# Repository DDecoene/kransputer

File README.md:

# kransputer

## What Kransputer is

Kransputer is a working computer built from a few thousand discrete CMOS
transistors — a machine on the scale of an Intel 4004, but made of parts you can
hold — designed to grow into a multiprocessor: one core, then a ring of up to
eight, passing messages the way INMOS's Transputer did. It exists to be
understood and rebuilt, by a person, a class or a hackerspace. Not to be sold.

## Why it looks the way it does

One decision forces everything else: CMOS. Almost every discrete-transistor
computer ever built is NMOS and burns about a watt standing still. CMOS costs
twice the transistors but makes power scale with clock rate instead — turn the
clock down and the machine sips. Staying inside a small transistor budget is why
the design is stripped to the bone:

- **One instruction** — subleq only, so there is no decoder. The instruction set
  lives in the assembler as macros.
- **A few bits at a time** — a serial datapath, so the arithmetic unit is a
  handful of adders. You pay in clock cycles, which are cheap.
- **No bus** — memory, display and input all speak SPI over four wires. No
  address bus, no data bus.

On this machine, talking to the core next door is cheaper than reading your own
memory. That is why the ring is the point, not an afterthought.

## How it gets built — from the ground up

The architecture is settled on paper: a SUBLEQ core with a serial datapath and
SPI links, meant to grow into a message-passing ring. What is deliberate is the
direction of the work. Instead of proving the whole machine on an FPGA before
touching a soldering iron, Kransputer is built upward from real gates, one
module at a time.

1. **Gates** — small PCBs, each a fistful of MOSFETs forming one logic function
   (NAND, NOR, NOT …), that plug into a breadboard and share a common bus. This
   is the layer built so far.
2. **Blocks** — those gates wired into the units the design calls for: the serial
   adder that is the whole ALU, the registers, the subleq sequencer and bit
   counter, the SPI interface to memory, the four-wire link to the next core.
   Each block is first modelled in structural Verilog — gate for gate, built
   from the same NAND/NOR/NOT cells as the boards — and checked in simulation,
   then built physically on breadboards.
3. **A core** — one complete processor, assembled from the blocks.
4. **A ring** — the core replicated and connected: two, then four, then eight,
   blocking on the links for synchronisation.

The structural model is the reference: the same stimulus into the simulation and
into the breadboard must give the same result, or the block is wrong.

## Status

The gate boards are drawn but **not yet routed** — schematics and rough
placement are done, copper is not. Work right now is on the first blocks in
structural Verilog, which land here soon. Once those hold up in simulation the
boards get routed and finished for a first self-ordered run, with build notes
and other material alongside.

## This repository

Discrete-logic building blocks for the kransputer — the **Gates** layer above.
Each module is a small PCB that plugs into a breadboard on two opposite edge
headers carrying an identical 16-pin pass-through bus, so modules can sit side by
side across one or more breadboards and be wired together into larger logic.

## Boards

| TARGET      | Board                                    |
|-------------|-------------------------------------------|
| `nand`      | 4x discrete static-CMOS 2-input NAND      |
| `nor`       | 4x discrete static-CMOS 2-input NOR       |
| `not`       | 6x discrete static-CMOS inverter          |
| `indicator` | 12-channel buffered bus LED indicator     |

Logic FETs are AO3400A (N-channel) / AO3401A (P-channel) in SOT-23.

The logic boards carry **no** indicator parts. Every node is on the bus; the
indicator board buffers each signal with a single AO3400A in common source (its
gate is high-impedance, so the logic net is not loaded) that sinks an LED fed
from the indicator board's own VDD rail. **LED lit = logic 1.** Watching the
machine therefore does not sag the logic levels.

## Bus pinout

Both edge headers (`J1`, `J2`) carry the same 16 pins, wired 1:1, so any signal
is reachable from either edge. Framing is fixed: pin 1 = VDD, pin 2 = GND,
pins 3–14 carry the 12 signal nets the board drives, pins 15/16 are the
edge-to-edge spares (`BUS_X`, `BUS_Y`).

`J1`/`J2` are stacking headers: male tails point down into the breadboard,
female sockets face up so the indicator shield can plug onto the same 16 pins.

### Signal nets per board (bus pins 3–14)

| Pin | `nand`   | `nor`   | `not`      | `indicator` |
|-----|----------|---------|------------|-------------|
| 3   | NAND_1_A | NOR_1_A | NOT_1_IN   | SIG1        |
| 4   | NAND_1_B | NOR_1_B | NOT_1_OUT  | SIG2        |
| 5   | NAND_1_Y | NOR_1_Y | NOT_2_IN   | SIG3        |
| 6   | NAND_2_A | NOR_2_A | NOT_2_OUT  | SIG4        |
| 7   | NAND_2_B | NOR_2_B | NOT_3_IN   | SIG5        |
| 8   | NAND_2_Y | NOR_2_Y | NOT_3_OUT  | SIG6        |
| 9   | NAND_3_A | NOR_3_A | NOT_4_IN   | SIG7        |
| 10  | NAND_3_B | NOR_3_B | NOT_4_OUT  | SIG8        |
| 11  | NAND_3_Y | NOR_3_Y | NOT_5_IN   | SIG9        |
| 12  | NAND_4_A | NOR_4_A | NOT_5_OUT  | SIG10       |
| 13  | NAND_4_B | NOR_4_B | NOT_6_IN   | SIG11       |
| 14  | NAND_4_Y | NOR_4_Y | NOT_6_OUT  | SIG12       |

The bus is positional: `J1` pin k ≡ `J2` pin k on every board. The indicator
shield taps pins 3–14 as `SIG1..SIG12` and shows whatever a neighbouring board
drives there.

Supply: 5 V on the bus. The two header rows are 0.9" apart (row `a` to row `j`
of one breadboard); columns b–e and f–i stay free for patch wires.

## Build

```bash
python3 -m venv venv
./venv/bin/pip install -r requirements.txt

./venv/bin/python circuit.py             # writes every <target>_module.net
./venv/bin/python circuit.py nand        # or just one
```

`kicad_env.py` finds the KiCad symbol libraries at the macOS bundle path
(`/Applications/KiCad/KiCad.app/...`). On Linux or Windows, set the
`KICAD*_SYMBOL_DIR` / `KICAD*_FOOTPRINT_DIR` environment variables to your
install's library paths before running, or adjust `kicad_env.py`.

1. Turn the netlist into a board. Either open a new PCB project `nand_module/`
   in KiCad and "Update PCB from Netlist", or run `kinet2pcb` headless (needs
   `skidl`, `kinparse` and `pcbnew` on the *same* Python — i.e. installed into
   KiCad's bundled Python, since `pcbnew` is not in the venv):
   ```bash
   kinet2pcb -i nand_module.net -o nand_module/nand_module.kicad_pcb -w --overwrite
   ```
2. Rough auto-placement — run from the folder that contains `nand_module/`,
   using KiCad's bundled Python:
   ```bash
   /Applications/KiCad/KiCad.app/Contents/Frameworks/Python.framework/Versions/3.9/bin/python3 \
       place.py nand
   ```
   `place.py` positions J1/J2 on opposite 0.9" edges, clusters each gate between
   them, draws a tight `Edge.Cuts` rectangle and pours a `B.Cu` GND zone. Pass an
   explicit `.kicad_pcb` path as a second argument to place a board elsewhere.
3. Reopen in KiCad, nudge, route. Re-fill the GND zone. Run DRC.
4. Plot Gerbers.

Repeat with `nor`, `not`, and `indicator` (each is its own KiCad project in its
own `<target>_module/` folder). `nand_module/`, `nor_module/`, `not_module/` and
`indicator_module/` are checked in.

### Fan-out

A discrete gate output driving other **gate** inputs is limited by speed, not
current (CMOS inputs are capacitive) — fine at this machine's speeds. One
indicator-board channel adds roughly the AO3400A gate capacitance to the net it
watches; one indicator board on the bus is negligible.

## Tests

```bash
./venv/bin/pytest
```

The placement integration test is skipped unless `kinet2pcb` can import
`pcbnew` (it cannot from the venv). `place.py` uses fixed, hand-computed
coordinates per board type, so its output is deterministic and easy to
eyeball in KiCad.

## Layout

- `circuit.py`  — SKiDL netlist generator (all boards, no arg = build every one)
- `place.py`    — pcbnew layout: exact positions per board type, Edge.Cuts, GND pour
- `kicad_env.py`— points SKiDL at the bundled KiCad libraries on macOS
- `SYMBOLS.md`  — resolved KiCad symbols (AO3400A/AO3401A, LED, R array, header)
- `tests/`      — SKiDL-netlist topology checks per board + CLI + place integration

## Licence

[PolyForm Noncommercial License 1.0.0](LICENSE). Build it, study it, modify it,
teach with it, and contribute — freely, for any noncommercial purpose. Selling
kits, boards, or hardware based on this work is reserved to the maintainer; see
[COMMERCIAL.md](COMMERCIAL.md). Contribution terms are in
[CONTRIBUTING.md](CONTRIBUTING.md).

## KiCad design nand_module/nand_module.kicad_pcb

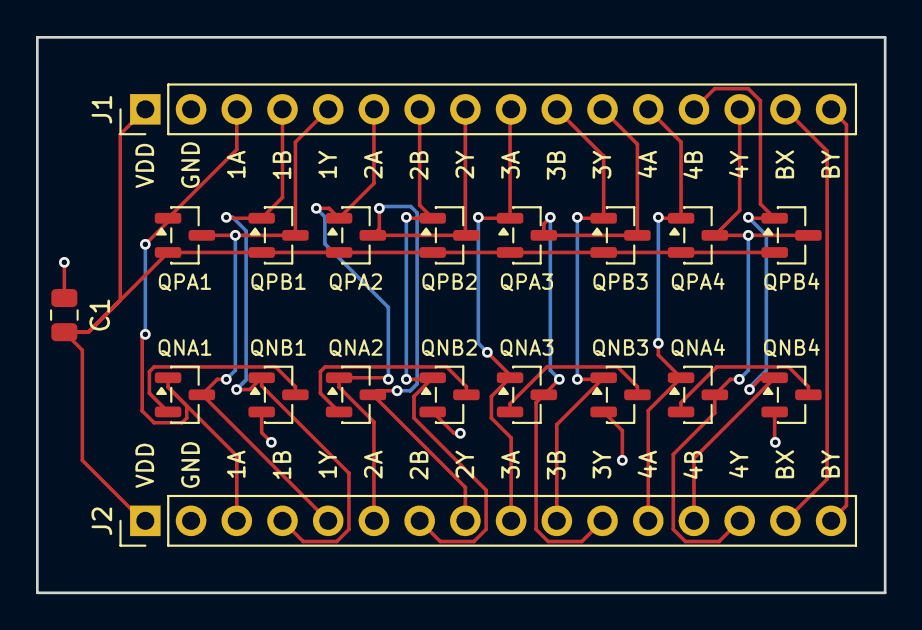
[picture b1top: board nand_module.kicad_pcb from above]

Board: 2 copper layers, 47.1 x 30.9 mm, 19 parts (0 on the bottom side), 20 nets.

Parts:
C1: 1u; C_0805_2012Metric
J1, J2: BUS_STACK_1x16; PinHeader_1x16_P2.54mm_Vertical
QNA1, QNA2, QNA3, QNA4: AO3400A; SOT-23
QNB1, QNB2, QNB3, QNB4: AO3400A; SOT-23
QPA1, QPA2, QPA3, QPA4: AO3401A; SOT-23
QPB1, QPB2, QPB3, QPB4: AO3401A; SOT-23

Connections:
BUS_X: J1.15, J2.15
BUS_Y: J1.16, J2.16
GND: C1.2, J1.2, J2.2, QNB1.2, QNB2.2, QNB3.2, QNB4.2
NAND_1_A: J1.3, J2.3, QNA1.1, QPA1.1
NAND_1_B: J1.4, J2.4, QNB1.1, QPB1.1
NAND_1_MID: QNA1.2, QNB1.3
NAND_1_Y: J1.5, J2.5, QNA1.3, QPA1.3, QPB1.3
NAND_2_A: J1.6, J2.6, QNA2.1, QPA2.1
NAND_2_B: J1.7, J2.7, QNB2.1, QPB2.1
NAND_2_MID: QNA2.2, QNB2.3
NAND_2_Y: J1.8, J2.8, QNA2.3, QPA2.3, QPB2.3
NAND_3_A: J1.9, J2.9, QNA3.1, QPA3.1
NAND_3_B: J1.10, J2.10, QNB3.1, QPB3.1
NAND_3_MID: QNA3.2, QNB3.3
NAND_3_Y: J1.11, J2.11, QNA3.3, QPA3.3, QPB3.3
NAND_4_A: J1.12, J2.12, QNA4.1, QPA4.1
NAND_4_B: J1.13, J2.13, QNB4.1, QPB4.1
NAND_4_MID: QNA4.2, QNB4.3
NAND_4_Y: J1.14, J2.14, QNA4.3, QPA4.3, QPB4.3
VDD: C1.1, J1.1, J2.1, QPA1.2, QPA2.2, QPA3.2, QPA4.2, QPB1.2, QPB2.2, QPB3.2, QPB4.2

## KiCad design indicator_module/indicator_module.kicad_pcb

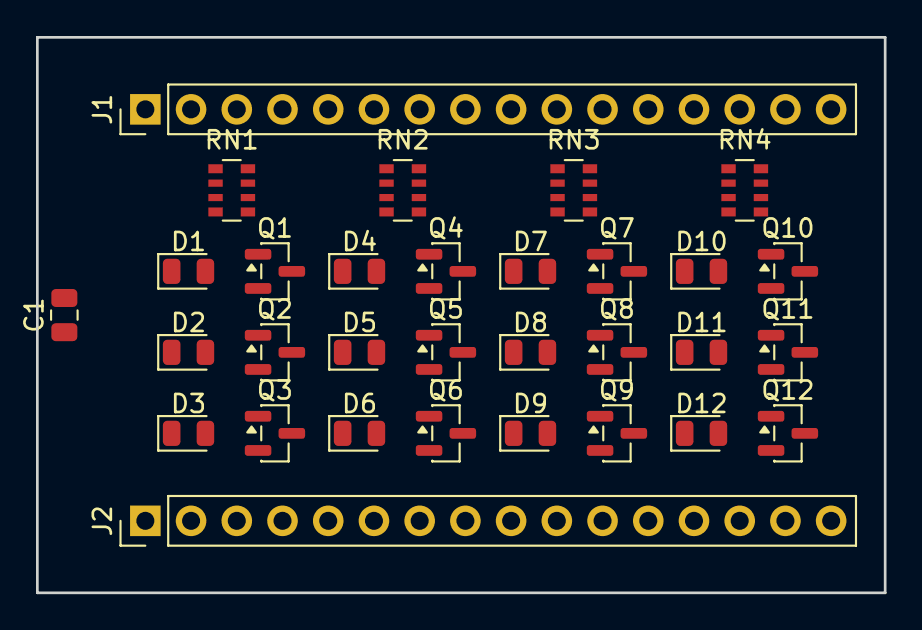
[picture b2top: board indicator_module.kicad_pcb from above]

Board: 2 copper layers, 47.1 x 30.9 mm, 31 parts (0 on the bottom side), 40 nets, no tracks yet.

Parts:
C1: 1u; C_0805_2012Metric
D1: D1; LED_0805_2012Metric
D2: D2; LED_0805_2012Metric
D3: D3; LED_0805_2012Metric
D4: D4; LED_0805_2012Metric
D5: D5; LED_0805_2012Metric
D6: D6; LED_0805_2012Metric
D7: D7; LED_0805_2012Metric
D8: D8; LED_0805_2012Metric
D9: D9; LED_0805_2012Metric
D10: D10; LED_0805_2012Metric
D11: D11; LED_0805_2012Metric
D12: D12; LED_0805_2012Metric
J1, J2: BUS_STACK_1x16; PinHeader_1x16_P2.54mm_Vertical
Q1, Q2, Q3, Q4, Q5, Q6, Q7, Q8, Q9, Q10, Q11, Q12: AO3400A; SOT-23
RN1, RN2, RN3, RN4: 1k; R_Array_Convex_4x0603

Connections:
BUS_X: J1.15, J2.15
BUS_Y: J1.16, J2.16
GND: C1.2, J1.2, J2.2, Q1.2, Q2.2, Q3.2, Q4.2, Q5.2, Q6.2, Q7.2, Q8.2, Q9.2, Q10.2, Q11.2, Q12.2, RN1.4, RN1.5, RN2.4, RN2.5, RN3.4, RN3.5, RN4.4, RN4.5
unnamed: D1.1, Q1.3
unnamed: D1.2, RN1.1
unnamed: D2.1, Q2.3
unnamed: D2.2, RN1.2
unnamed: D3.1, Q3.3
unnamed: D3.2, RN1.3
unnamed: D4.1, Q4.3
unnamed: D4.2, RN2.1
unnamed: D5.1, Q5.3
unnamed: D5.2, RN2.2
unnamed: D6.1, Q6.3
unnamed: D6.2, RN2.3
unnamed: D7.1, Q7.3
unnamed: D7.2, RN3.1
unnamed: D8.1, Q8.3
unnamed: D8.2, RN3.2
unnamed: D9.1, Q9.3
unnamed: D9.2, RN3.3
unnamed: D10.1, Q10.3
unnamed: D10.2, RN4.1
unnamed: D11.1, Q11.3
unnamed: D11.2, RN4.2
unnamed: D12.1, Q12.3
unnamed: D12.2, RN4.3
SIG1: J1.3, J2.3, Q1.1
SIG2: J1.4, J2.4, Q2.1
SIG3: J1.5, J2.5, Q3.1
SIG4: J1.6, J2.6, Q4.1
SIG5: J1.7, J2.7, Q5.1
SIG6: J1.8, J2.8, Q6.1
SIG7: J1.9, J2.9, Q7.1
SIG8: J1.10, J2.10, Q8.1
SIG9: J1.11, J2.11, Q9.1
SIG10: J1.12, J2.12, Q10.1
SIG11: J1.13, J2.13, Q11.1
SIG12: J1.14, J2.14, Q12.1
VDD: C1.1, J1.1, J2.1, RN1.6, RN1.7, RN1.8, RN2.6, RN2.7, RN2.8, RN3.6, RN3.7, RN3.8, RN4.6, RN4.7, RN4.8

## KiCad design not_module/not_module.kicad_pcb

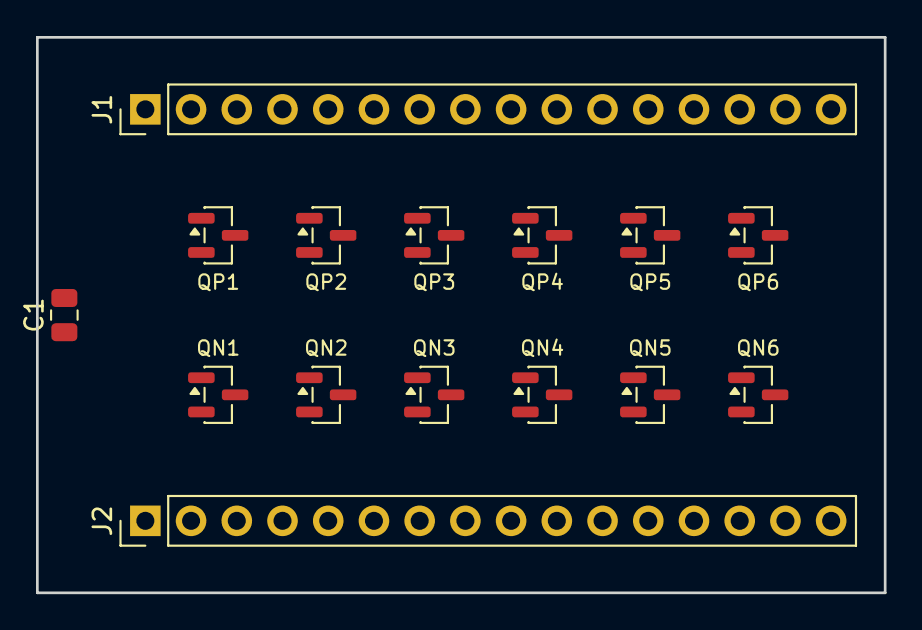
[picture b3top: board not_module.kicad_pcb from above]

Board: 2 copper layers, 47.1 x 30.9 mm, 15 parts (0 on the bottom side), 16 nets, no tracks yet.

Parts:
C1: 1u; C_0805_2012Metric
J1, J2: BUS_STACK_1x16; PinHeader_1x16_P2.54mm_Vertical
QN1, QN2, QN3, QN4, QN5, QN6: AO3400A; SOT-23
QP1, QP2, QP3, QP4, QP5, QP6: AO3401A; SOT-23

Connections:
BUS_X: J1.15, J2.15
BUS_Y: J1.16, J2.16
GND: C1.2, J1.2, J2.2, QN1.2, QN2.2, QN3.2, QN4.2, QN5.2, QN6.2
NOT_1_IN: J1.3, J2.3, QN1.1, QP1.1
NOT_1_OUT: J1.4, J2.4, QN1.3, QP1.3
NOT_2_IN: J1.5, J2.5, QN2.1, QP2.1
NOT_2_OUT: J1.6, J2.6, QN2.3, QP2.3
NOT_3_IN: J1.7, J2.7, QN3.1, QP3.1
NOT_3_OUT: J1.8, J2.8, QN3.3, QP3.3
NOT_4_IN: J1.9, J2.9, QN4.1, QP4.1
NOT_4_OUT: J1.10, J2.10, QN4.3, QP4.3
NOT_5_IN: J1.11, J2.11, QN5.1, QP5.1
NOT_5_OUT: J1.12, J2.12, QN5.3, QP5.3
NOT_6_IN: J1.13, J2.13, QN6.1, QP6.1
NOT_6_OUT: J1.14, J2.14, QN6.3, QP6.3
VDD: C1.1, J1.1, J2.1, QP1.2, QP2.2, QP3.2, QP4.2, QP5.2, QP6.2

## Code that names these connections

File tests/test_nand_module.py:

import re

import circuit
from skidl import Net
from helpers import circuit as active_circuit, net_by_name, pins_named, pins_numbered


def _one_gate():
    a, b, y = Net("NAND_1_A"), Net("NAND_1_B"), Net("NAND_1_Y")
    vdd, gnd = Net("VDD"), Net("GND")
    circuit.nand_gate(1, a, b, y, vdd, gnd)


def test_nand_gate_has_four_semantic_transistors():
    _one_gate()
    parts = active_circuit().parts
    refs = {p.ref for p in parts}
    assert refs == {"QPA1", "QPB1", "QNA1", "QNB1"}
    vals = {p.ref: p.value for p in parts}
    assert vals["QPA1"] == "AO3401A"
    assert vals["QNA1"] == "AO3400A"


def test_nand_gate_topology():
    _one_gate()
    assert pins_named(net_by_name("NAND_1_A")) == {("QPA1", "G"), ("QNA1", "G")}
    assert pins_named(net_by_name("NAND_1_B")) == {("QPB1", "G"), ("QNB1", "G")}
    assert pins_named(net_by_name("VDD")) == {("QPA1", "S"), ("QPB1", "S")}
    assert pins_named(net_by_name("NAND_1_Y")) == {
        ("QPA1", "D"), ("QPB1", "D"), ("QNA1", "D")}
    assert pins_named(net_by_name("NAND_1_MID")) == {
        ("QNA1", "S"), ("QNB1", "D")}
    assert pins_named(net_by_name("GND")) == {("QNB1", "S")}


def test_nand_gate_footprints_are_sot23():
    _one_gate()
    assert all(p.footprint == circuit.FP_SOT23
               for p in active_circuit().parts)


def test_assemble_nand_module_part_counts():
    circuit.assemble_nand_module()
    parts = active_circuit().parts
    assert len([p for p in parts if p.value == "AO3401A"]) == 8
    assert len([p for p in parts if p.value == "AO3400A"]) == 8
    assert {p.ref for p in parts if p.ref.startswith("J")} == {"J1", "J2"}
    assert [p.ref for p in parts if p.ref == "C1"] == ["C1"]
    assert not [p for p in parts if p.value == "LED"]


def test_assemble_nand_module_bus_wiring():
    circuit.assemble_nand_module()
    j1 = next(p for p in active_circuit().parts if p.ref == "J1")
    assert j1[5].net.name == "NAND_1_Y"
    assert j1[8].net.name == "NAND_2_Y"
    assert j1[14].net.name == "NAND_4_Y"
    assert pins_numbered(net_by_name("BUS_X")) == {("J1", "15"), ("J2", "15")}


def test_assemble_nand_module_bulk_cap_across_rails():
    circuit.assemble_nand_module()
    assert ("C1", "1") in pins_numbered(net_by_name("VDD"))
    assert ("C1", "2") in pins_numbered(net_by_name("GND"))


def test_build_nand_module_writes_netlist(tmp_path, monkeypatch):
    monkeypatch.chdir(tmp_path)
    circuit.build_nand_module()
    out = tmp_path / "nand_module.net"
    assert out.exists()
    comps = re.findall(r"\(comp\s", out.read_text())
    assert len(comps) == 19   # 16 FET + C1 + J1 + J2

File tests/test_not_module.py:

import re

import circuit
from skidl import Net
from helpers import circuit as active_circuit, net_by_name, pins_named, pins_numbered


def _one_gate():
    vin, vout = Net("NOT_1_IN"), Net("NOT_1_OUT")
    vdd, gnd = Net("VDD"), Net("GND")
    circuit.not_gate(1, vin, vout, vdd, gnd)


def test_not_gate_has_two_semantic_transistors():
    _one_gate()
    parts = active_circuit().parts
    assert {p.ref for p in parts} == {"QP1", "QN1"}
    vals = {p.ref: p.value for p in parts}
    assert vals["QP1"] == "AO3401A"
    assert vals["QN1"] == "AO3400A"


def test_not_gate_topology():
    _one_gate()
    assert pins_named(net_by_name("NOT_1_IN")) == {("QP1", "G"), ("QN1", "G")}
    assert pins_named(net_by_name("VDD")) == {("QP1", "S")}
    assert pins_named(net_by_name("GND")) == {("QN1", "S")}
    assert pins_named(net_by_name("NOT_1_OUT")) == {("QP1", "D"), ("QN1", "D")}


def test_not_gate_footprints_are_sot23():
    _one_gate()
    assert all(p.footprint == circuit.FP_SOT23 for p in active_circuit().parts)


def test_assemble_not_module_part_counts():
    circuit.assemble_not_module()
    parts = active_circuit().parts
    assert len([p for p in parts if p.value == "AO3401A"]) == 6
    assert len([p for p in parts if p.value == "AO3400A"]) == 6
    assert {p.ref for p in parts if p.ref.startswith("J")} == {"J1", "J2"}
    assert [p.ref for p in parts if p.ref == "C1"] == ["C1"]
    assert not [p for p in parts if p.value == "LED"]


def test_assemble_not_module_bus_wiring():
    circuit.assemble_not_module()
    j1 = next(p for p in active_circuit().parts if p.ref == "J1")
    assert j1[3].net.name == "NOT_1_IN"
    assert j1[4].net.name == "NOT_1_OUT"
    assert j1[14].net.name == "NOT_6_OUT"
    assert pins_numbered(net_by_name("BUS_X")) == {("J1", "15"), ("J2", "15")}


def test_assemble_not_module_bulk_cap_across_rails():
    circuit.assemble_not_module()
    assert ("C1", "1") in pins_numbered(net_by_name("VDD"))
    assert ("C1", "2") in pins_numbered(net_by_name("GND"))


def test_build_not_module_writes_netlist(tmp_path, monkeypatch):
    monkeypatch.chdir(tmp_path)
    circuit.build_not_module()
    out = tmp_path / "not_module.net"
    assert out.exists()
    comps = re.findall(r"\(comp\s", out.read_text())
    assert len(comps) == 15   # 12 FET + C1 + J1 + J2

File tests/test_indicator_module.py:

import circuit
from skidl import Net
from helpers import circuit as active_circuit, net_by_name, pins_named, pins_numbered


def _one_group():
    s1, s2, s3 = Net("SIG1"), Net("SIG2"), Net("SIG3")
    vdd, gnd = Net("VDD"), Net("GND")
    circuit.indicator_gate(1, s1, s2, s3, vdd, gnd)


def _part(ref):
    return next(p for p in active_circuit().parts if p.ref == ref)


def test_indicator_group_parts():
    _one_group()
    refs = {p.ref for p in active_circuit().parts}
    assert {"Q1", "Q2", "Q3"} <= refs   # buffer FETs, running index
    assert {"D1", "D2", "D3"} <= refs   # LEDs
    assert "RN1" in refs                # resistor array for the group
    led = _part("D1")
    assert led.value == "D1"
    assert led.footprint == circuit.FP_LED
    assert _part("Q1").value == "AO3400A"


def test_indicator_group_channel_topology():
    _one_group()
    # AO3400A common source: source -> GND, gate -> bus signal
    assert ("Q2", "G") in pins_named(net_by_name("SIG2"))
    assert ("Q2", "S") in pins_named(net_by_name("GND"))
    # LED cathode ties to the FET drain (private net)
    d, q = _part("D2"), _part("Q2")
    assert d["K"].net is q["D"].net
    assert d["K"].net.name not in ("VDD", "GND", "SIG2")
    # LED anode goes to the array
    assert ("RN1", "2") in pins_named(d["A"].net) or \
           ("RN1", "2") in pins_numbered(d["A"].net)


def test_indicator_group_array_feeds_vdd_and_parks_spare():
    _one_group()
    vdd = pins_numbered(net_by_name("VDD"))
    gnd = pins_numbered(net_by_name("GND"))
    assert {("RN1", "8"), ("RN1", "7"), ("RN1", "6")} <= vdd   # 3 channels VDD side
    assert {("RN1", "4"), ("RN1", "5")} <= gnd                 # spare R4 parked


def test_second_group_continues_the_running_index():
    s4, s5, s6 = Net("SIG4"), Net("SIG5"), Net("SIG6")
    vdd, gnd = Net("VDD"), Net("GND")
    circuit.indicator_gate(2, s4, s5, s6, vdd, gnd)
    refs = {p.ref for p in active_circuit().parts}
    assert {"Q4", "Q5", "Q6", "D4", "D5", "D6", "RN2"} <= refs
    assert ("Q5", "G") in pins_named(net_by_name("SIG5"))


def test_assemble_indicator_module_counts():
    circuit.assemble_indicator_module()
    parts = active_circuit().parts
    assert len([p for p in parts if p.value == "AO3400A"]) == 12
    assert len([p for p in parts if p.footprint == circuit.FP_LED]) == 12
    assert sorted(p.ref for p in parts if p.ref.startswith("RN")) == \
        ["RN1", "RN2", "RN3", "RN4"]
    assert sorted((p.ref for p in parts if p.ref.startswith("D")),
                  key=lambda r: int(r[1:])) == [f"D{i}" for i in range(1, 13)]
    assert {p.ref for p in parts if p.ref.startswith("J")} == {"J1", "J2"}
    assert [p.ref for p in parts if p.ref == "C1"] == ["C1"]
    assert not [p for p in parts if p.value == "AO3401A"]


def test_assemble_indicator_module_bus_reaches_buffers():
    circuit.assemble_indicator_module()
    j1 = next(p for p in active_circuit().parts if p.ref == "J1")
    assert j1[10].net.name == "SIG8"                    # bus pin 10 -> SIG(10-2)
    assert ("Q8", "G") in pins_named(net_by_name("SIG8"))


def test_build_indicator_module_writes_netlist(tmp_path, monkeypatch):
    monkeypatch.chdir(tmp_path)
    circuit.build_indicator_module()
    assert (tmp_path / "indicator_module.net").exists()
